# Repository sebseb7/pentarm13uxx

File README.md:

pentarm13uxx
============

a small template project (blinking led) for the new lpc1347 (successor of the popular lpc1343)

including Makefile, linker-script and cmsis and microcontroler header files

also includes eagle files for a small breaboardable eval-board

- - -

####lpc1347 features

* 12k sram (was 8k)
* 64k flash (was 32k)
* 4k EEPROM (new)
* 72Mhz
* USART,I2C,2xSPI
* 12Bit ADC (new)
* USB_MSC, USB_HID, USB_CDC and USB_DFU in rom (new)
* usb-bootloader in rom

- - -

price of the eval board: ~$15

- - -

####BOM:

* C1,C2 : 22pF 0402
* C3,C4 : 100nF 0402
* C6,C8 : 10nF 0402
* C5,C7 : 1µF 0805
* R2,R3,R6,R7 : 150R 0402
* R4,R5 : 33R 0402
* R1,R8,R9 : 15k 0402
* R10 : 1k5 0402
* T1 : Si3102DS SOT23 (or other pfet)
* Q1 : 12Mhz MT (farnell: 1842056)
* IC1 : lpc1347 QFP48 (farnell: 2103477)
* IC2 : LT1763CS8-3.3 SOIC8 (farnell: 1273617)
* X1 : Mini USB Connector SMD (farnell: 1125348)
* X2,X3 : Pin-Header 10 Pin
* X4 : Pin Header 2 Pin
* X5 : Pin Header 4 Pin
* LED1,LED2 : Smd LED 0805
* SW1,SW2,RST : MCTAEF-25N (farnell:1605484)

- - -

data sheet  : http://www.nxp.com/documents/data_sheet/LPC1315_16_17_45_46_47.pdf

user manual : http://www.nxp.com/documents/user_manual/UM10524.pdf

toolchain   : https://launchpad.net/gcc-arm-embedded

- - -

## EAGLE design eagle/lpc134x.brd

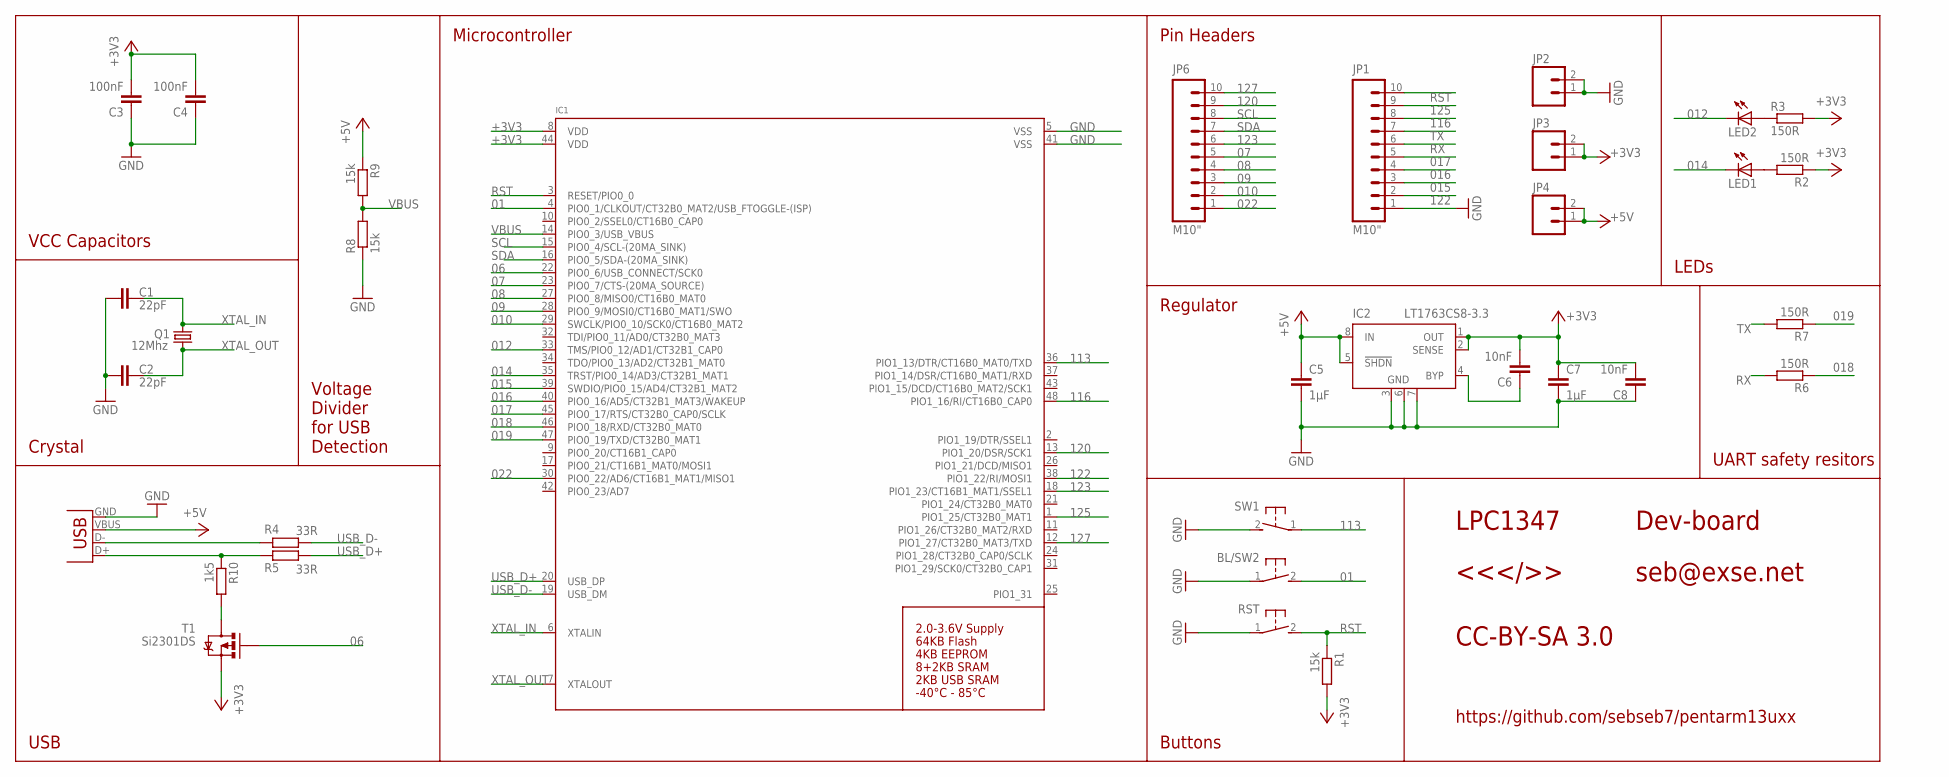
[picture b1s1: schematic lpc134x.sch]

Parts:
BL/SW2: SWITCH_MCTAEF
C1, C2: 22pF; C0402
C3, C4: 100nF; C0402
C5, C7: 1µF; 0805
C6, C8: 10nF; C0402
IC1: LPC1347_QFP48; LQFP48
IC2: LT1763CS8-3.3; SOIC8
JP1, JP6: M10"; 1X10
JP2, JP3, JP4: M02PTH; 1X02
LED1, LED2: LEDCHIPLED_0805; CHIPLED_0805
Q1: 12Mhz; MT
R1, R8, R9: 15k; R0402
R2, R3, R6, R7: 150R; R0402
R4, R5: 33R; R0402
R10: 1k5; R0402
RST: SWITCH_MCTAEF
SW1: SWITCH_MCTAEF
T1: Si2301DS; SOT23
X2: USB-SMD-NS; USB-MINIB-NOSTOP

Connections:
01: BL/SW2.2, IC1.4 (PIO0_1/CLKOUT/CT32B0_MAT2/USB_FTOGGLE-(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)
06: IC1.22 (PIO0_6/USB_CONNECT/SCK0), T1.1 (G)
07: IC1.23 (PIO0_7/CTS-(20MA_SOURCE)), JP6.5
08: IC1.27 (PIO0_8/MISO0/CT16B0_MAT0), JP6.4
09: IC1.28 (PIO0_9/MOSI0/CT16B0_MAT1/SWO), JP6.3
010: IC1.29 (SWCLK/PIO0_10/SCK0/CT16B0_MAT2), JP6.2
012: IC1.33 (TMS/PIO0_12/AD1/CT32B1_CAP0), LED2.C
014: IC1.35 (TRST/PIO0_14/AD3/CT32B1_MAT1), LED1.C
015: IC1.39 (SWDIO/PIO0_15/AD4/CT32B1_MAT2), JP1.3
016: IC1.40 (PIO0_16/AD5/CT32B1_MAT3/WAKEUP), JP1.4
017: IC1.45 (PIO0_17/RTS/CT32B0_CAP0/SCLK), JP1.5
018: IC1.46 (PIO0_18/RXD/CT32B0_MAT0), R6.1
019: IC1.47 (PIO0_19/TXD/CT32B0_MAT1), R7.1
022: IC1.30 (PIO0_22/AD6/CT16B1_MAT1/MISO1), JP6.1
113: IC1.36 (PIO1_13/DTR/CT16B0_MAT0/TXD), SW1.1
116: IC1.48 (PIO1_16/RI/CT16B0_CAP0), JP1.8
120: IC1.13 (PIO1_20/DSR/SCK1), JP6.9
122: IC1.38 (PIO1_22/RI/MOSI1), JP1.2
123: IC1.18 (PIO1_23/CT16B1_MAT1/SSEL1), JP6.6
125: IC1.1 (PIO1_25/CT32B0_MAT1), JP1.9
127: IC1.12 (PIO1_27/CT32B0_MAT3/TXD), JP6.10
+3V3: C3.2, C4.2, C6.2, C7.1, C8.2, IC1.8 (VDD), IC1.44 (VDD), IC2.1 (OUT), IC2.2 (SENSE), JP3.1, JP3.2, R1.2, R2.1, R3.2, T1.2 (S)
+5V: C5.1, IC2.5 (!SHDN), IC2.8 (IN), JP4.1, JP4.2, R9.1, X2.VBUS
GND: BL/SW2.1, C1.1, C2.1, C3.1, C4.1, C5.2, C7.2, C8.1, IC1.5 (VSS), IC1.41 (VSS), IC2.3 (GND), IC2.6 (GND), IC2.7 (GND), JP1.1, JP2.1, JP2.2, R8.1, RST.1, SW1.2, X2.GND
unnamed: R5.2, R10.1, X2.D+
unnamed: R4.2, X2.D-
unnamed: C6.1, IC2.4 (BYP)
unnamed: LED1.A, R2.2
unnamed: R10.2, T1.3 (D)
unnamed: LED2.A, R3.1
RST: IC1.3 (RESET/PIO0_0), JP1.10, R1.1, RST.2
RX: JP1.6, R6.2
SCL: IC1.15 (PIO0_4/SCL-(20MA_SINK)), JP6.8
SDA: IC1.16 (PIO0_5/SDA-(20MA_SINK)), JP6.7
TX: JP1.7, R7.2
USB_D+: IC1.20 (USB_DP), R5.1
USB_D-: IC1.19 (USB_DM), R4.1
VBUS: IC1.14 (PIO0_3/USB_VBUS), R8.2, R9.2
XTAL_IN: C1.2, IC1.6 (XTALIN), Q1.3 (2)
XTAL_OUT: C2.2, IC1.7 (XTALOUT), Q1.1

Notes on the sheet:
Pin Headers
Regulator
Buttons
LEDs
UART safety resitors
Microcontroller
Voltage Divider for USB Detection
Crystal
VCC Capacitors
USB
CC-BY-SA 3.0
seb@exse.net
<<</>>
LPC1347
Dev-board
https://github.com/sebseb7/pentarm13uxx

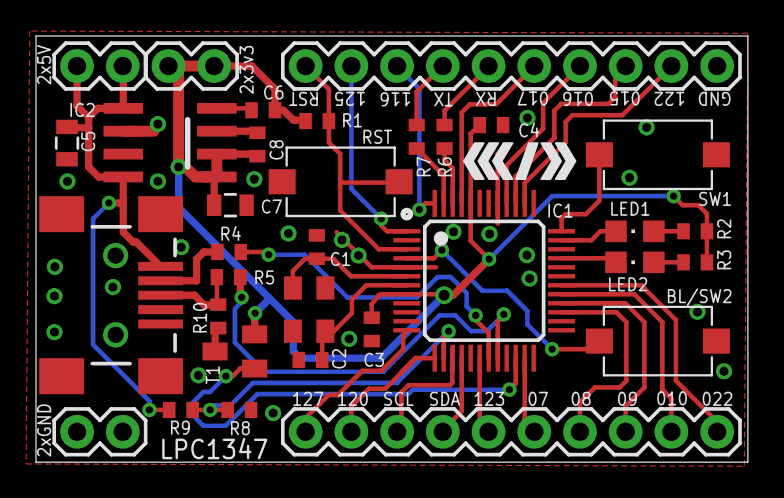
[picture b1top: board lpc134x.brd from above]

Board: 2 copper layers, 39.5 x 23.7 mm, 34 parts (0 on the bottom side), 40 nets.

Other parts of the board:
U$2: C3D2_LOGO_SMALL

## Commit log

2012-09-13 init
2012-09-13 added linker script and startup code (experimental)
2012-09-13 differend linkerscript
2012-09-13 obsolete for gcc
2012-09-13 detect disc
2012-09-13 minor gcc flag changed
2012-09-13 -O2 -> -O1
2012-09-14 compiler options madness & asm listing output
2012-09-14 working !
2012-09-14 pcb image
2012-09-14 eagle files
2012-09-14 added brd picture
2012-09-14 missing file
2012-09-14 values
2012-09-14 added usb cdc example
2012-09-14 fixes
2012-09-17 template for shields
2012-10-01 pretty
2012-10-01 even prettieer
2012-10-06 drivers for oled & i2c joystick
2012-10-06 added libs and drivers
2012-10-06 libs
2012-10-06 changed to simple blink
2012-10-06 not use drivers in blinky-example
2012-10-06 usb_cdc driver
2012-10-06 moved
2012-10-06 uncomplete bmp085 driver
2012-10-06 nearing completion
2012-10-06 made some functions static
2012-10-06 bmp driver demo
2012-10-09 fixed temperature calculation implementation error
2012-10-09 bmp085 driver completed
2012-10-15 images
2012-10-15 wrong files
2012-11-03 correct 6800 mode
2012-12-20 cleanup
2012-12-20 toolchain link
2012-12-20 pcb update
2013-02-03 updated toolchain link
2013-02-03 fixed image links
2013-02-22 reorg
2013-04-27 cmsis 3.2

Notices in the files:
parts and their libraries:
SparkFun-Connectors: Licensing: CC v3.0 Share-Alike You are welcome to use this library for commercial purposes.
